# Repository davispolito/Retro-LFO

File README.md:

=======

## The Problem
With only 1-2 wave analog waveforms, LFOs on older synthesizers, specifically the moog prodigy, are severely limited in their capabilities. Since LFOs are control functions and do not directly enter into the audio output, there is no benefit of the circuitry that initially creates these functions. These synthesizers would be better served by a more robust LFO design.
`

## The Solution
Utilizing an Attiny45 I have developed an LFO that can be retrofitted into synthesizers to increase LFO functions. These would include square (bipolar and unipolar), saw, reverse saw, triangle, sine and sample, and hold waveforms. This solution is cost effective using an 8 bit microcontroller that costs under a dollar, and minimal analog components.
 
## The algorithms 
Algorithms for the LFO shapes are simple and concise. By varying a PWM utility on the Attiny, we output a varying pulse square wave that once filtered creates smooth control functions.

### Saw 
```
uint8_t sawtooth(uint8_t* step){
	(*step)++;
	return *step;
}
```

### Reverse Saw
```
uint8_t reversesaw(uint8_t* step){
	(*step)--;

	return *step;
}
```

### Triangle 
```
uint8_t triangle(uint8_t* step){
	static int ud = 0;
	if (ud){
		*step -= 2;
		if(!*step){
			ud = 0;
		}
		} else {
		*step += 2;
		if (*step == 254){
			ud = 1;
		}
	}
	return *step;
}
```

### Unipolar Square 
```
uint8_t square_p(uint8_t* count){
	static int freq = 126;
	(*count)++;
	static uint8_t val = 0x7F;
	if(*count < freq){
		val = 0x7F;
		} else {
		val = 0xFE;
	}
	*count %= 2*freq;

	return val;
}

uint8_t square_n(uint8_t* count){
	static int freq = 126;
	(*count)++;
	static uint8_t val = 0x01;
	if(*count < freq){
		val = 0x01;
		} else {
		val = 0x7F;
	}
	*count %= 2*freq;
	
	return val;
}
```
### Bipolar Square
```
uint8_t square_f(uint8_t* count){

	static int freq = 126;
	(*count)++;
	static uint8_t val = 0x01;
	if(*count < freq){
		val = 0x01;
		} else {
		val = 0xFE;
	}
	*count %= 2*freq;

	return val;
}
```

### Sample and Hold
```
uint8_t sampleAndHold(uint8_t* count){
	static uint8_t b = 0;
	static uint8_t i = 0;
	if(i == 0){
		int a = rand();
		b = 0xFF & a;
	}
	//(*count)++;
	
	return b;
}
``` 
Note: After some time it was determined that the random function was more reliably random than an LFSR. I hope to modify this code to include a modified call to my machine code routine for white noise generation so that I do not need library calls and can keep the program as lightweight as possible. 

### Sine

```
uint8_t sinewave_(uint8_t* i){
	uint8_t val = pgm_read_byte(&sinewave[(*i)++]) / mod_scale + 128 - (256/(mod_scale * 2));
	(*i) %= 256;
	return val;
}
```

## Varying the Frequency
In order to vary the Frequency, I implemented a delay function as well as a mapping function to take my inputs from the ADCs and map them to a piecewise logarithmic modeling function to bring the frequency from 0.3 Hz to 30Hz

 ```
 uint16_t map_m(uint16_t input_end, uint16_t        input_start, uint16_t output_end,               uint16_t output_start,  uint16_t input){
	uint16_t slope = (output_end - output_start) / (input_end - input_start);
	uint16_t output = output_start + slope * (input - input_start);
	return output;
}

int16_t VoltageToDelay (uint16_t volt){
	if(volt < 500){
		return map_m(500, 50, 800, 60, volt);
	} else {
		return map_m(1024, 500, 9200, 700, volt);
	}
	
	return 60 + (volt * 4);			//9000 top value (.3 Hz)  60 - 30 Hz
}

 ```

### Feature Freak
In developing the LFO, we aimed to be as thorough as possible. We utilized all 8 pins on the Attiny45. 

#### 3 Control Pots
By adding a third pot, we tried to implement new effects. One, an amplitude varying waveform based off timing determined by the third pot. We soon learned that reading 3 pots this quickly causes system failure. Delays and skips would occur, ruining our waveform. One possible solution for this would be implementing a rigorous RTOS, though I have yet to attempt implementation.  

Instead, we decided to create a button that would allow modes to be switched and the time varying amplitude to become one of the two control functions, replacing the waveform chooser. It is important that musicians have access to the effects they are using and we hope that this tradeoff will still benefit them.

#### Varying Amplitude with Phase Modulation and Interpolation/Dithering
    The low 12-bit resolution of our PWM forced us to resort to clever bit calculations in an attempt to smooth low amplitude wave forms. As we reduce amplitude, we reduce our bit resolution since we are only afforded smaller values. We are only able to use the least significant byte of our available bits when faced with a signal at half the amplitude. In order to get around this, we attempted a version of interpolation through dithering. When at intermediate phases of a waveform — whenever there are x number of steps between the current sample and the next sample — we switch between the available bits to simulate higher bit resolution.
Unfortunately this did not give us much greater resolution. 

Additionally, in order to create the amplitude variation, we implemented a phasing system. By combining a waveform out of phase with the output waveform, amplitude can be reduced or increased. In order to vary the amplitude, I simply varied the phase of a following waveform until the time step finished. 

```
uint8_t dither_up(uint8_t old_val, uint8_t new_val, uint8_t og_delay, uint8_t curr_delay){
	uint8_t difference = new_val - old_val;
	uint8_t num_cycles = og_delay / CYCLE_US;
	uint8_t curr_cycle = curr_delay / CYCLE_US;
	switch (difference){
		case 1 : {
			if(curr_cycle % 2) {
				return new_val;
				} else {
				return old_val;
			}
			break;
		}
		case 2: {
			uint16_t scaled = (100*curr_cycle) / num_cycles;
			if(scaled <= 33){
				return old_val;
			} else if (scaled <= 66){
				return old_val + 1;
			} else {
				return old_val + 2;
			}
			break;
		}
		case 3: {
			uint16_t scaled = (100*curr_cycle) / num_cycles;
			if(scaled <= 25){
				return old_val;
			} else if (scaled <= 50){
				return old_val + 1;
			} else if (scaled <= 75){
				return old_val + 2;
			} else {
				return old_val + 3;
			}
			break;
		}
	}
}
```
```
uint8_t dither_down(uint8_t old_val, uint8_t new_val, uint8_t og_delay, uint8_t curr_delay){
	uint8_t difference = old_val - new_val;
	uint8_t num_cycles = og_delay / CYCLE_US;
	uint8_t curr_cycle = curr_delay / CYCLE_US;
	switch (difference){
		case 1 : {
			if(curr_cycle % 2) {
				return new_val;
				} else {
				return old_val;
			}
			break;
		}
		default: {
			uint16_t scaled = (100*curr_cycle) / num_cycles;
			if(scaled <= 33){
				return old_val;
				} else if (scaled <= 66){
				return old_val - 1;
				} else {
				return old_val - 2;
			}
			break;
		}
	}
}
```
```
uint8_t dither(int16_t delay, uint8_t old_val){
	uint8_t next_val = wave_ptr(&i);// / mod_scale  + 128 - (256/(mod_scale * 2)); 
	uint8_t h = i + 100;
	uint8_t phaseOffset = wave_ptr(&h);
	//successive approx
	if(half < 16){
		if(next_val >= 128){
			next_val += (256/(mod_scale*half));
		}
		else {
			next_val -= (256/(mod_scale*half));
		}
	}
	int8_t difference;
	uint8_t og_delay = delay;
	while (delay > CYCLE_US * 3){
		if((difference = old_val - next_val) <= 3 && difference > 0){
			OCR0A = dither_down(old_val, next_val, og_delay, delay);
			} else if (difference >= -3 && difference < 0){
			OCR0A = dither_up(old_val, next_val, og_delay, delay);
		}
		_delay_us(CYCLE_US);
		delay = delay - CYCLE_US;
		
	}
	while(delay){
		_delay_us(1);
		delay--;
	}
	uint8_t phased = next_val + phaseOffset;
	if(phased < next_val){
		phased = 256 - phased; 
	}
	return next_val + phased;
}
```

# Future Plans
The plan for the Retro-LFO is to develop a PCB and begin offering it as an enhancement during synthesizer repairs at Retrolinear, as well as market it to eurorack enthusiasts on the web.

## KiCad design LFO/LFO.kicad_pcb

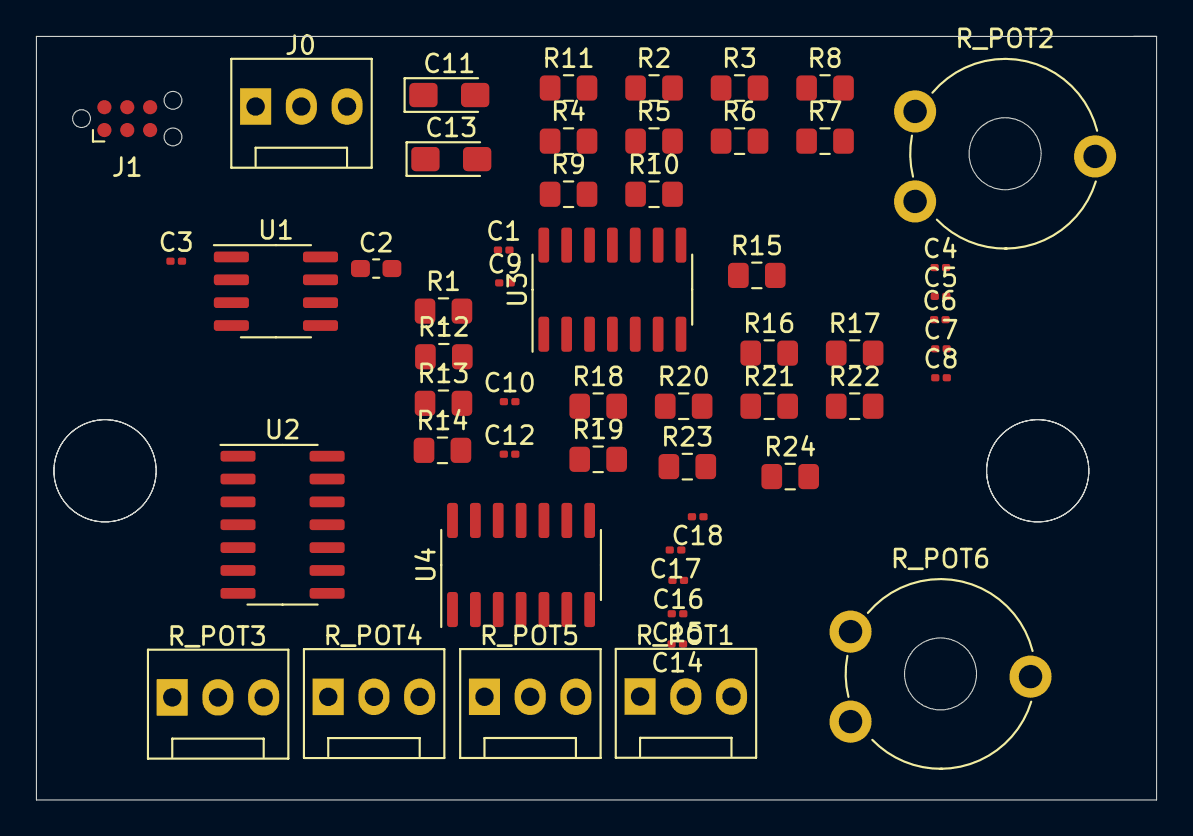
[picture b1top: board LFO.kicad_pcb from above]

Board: 2 copper layers, 62.2 x 42.4 mm, 54 parts (0 on the bottom side), 42 nets, no tracks yet.

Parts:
C1, C4, C9, C10, C12, C14: .1uF; C_0201_0603Metric
C2: .33uF; C_0603_1608Metric_Pad1.05x0.95mm_HandSolder
C3: .01uF; C_0201_0603Metric
C5, C7, C15, C17: 5.6nF; C_0201_0603Metric
C6, C8, C16, C18: 6.8nF; C_0201_0603Metric
C11, C13: 10uF; CP_EIA-3216-10_Kemet-I_Pad1.58x1.35mm_HandSolder
J0: Conn_01x03_Female; FanPinHeader_1x03_P2.54mm_Vertical
J1: AVR-ISP-6; Tag-Connect_TC2030-IDC-NL_2x03_P1.27mm_Vertical
R1, R2, R12, R13, R14, R15: 1k; R_0805_2012Metric_Pad1.15x1.40mm_HandSolder
R3, R4, R5, R6, R16, R17, R18, R19: 20k; R_0805_2012Metric_Pad1.15x1.40mm_HandSolder
R7, R20: 183k; R_0805_2012Metric_Pad1.15x1.40mm_HandSolder
R8, R21: 25k; R_0805_2012Metric_Pad1.15x1.40mm_HandSolder
R9, R11, R22, R24: 220k; R_0805_2012Metric_Pad1.15x1.40mm_HandSolder
R10, R23: 85k; R_0805_2012Metric_Pad1.15x1.40mm_HandSolder
R_POT1, R_POT3, R_POT4, R_POT5: 10k; FanPinHeader_1x03_P2.54mm_Vertical
R_POT2, R_POT6: 10k; Potentiometer_Piher_PT-10-V10_Vertical_Hole
U1: L78L05_SO8; SOIC-8_3.9x4.9mm_P1.27mm
U2: ATtiny44A-PU; SOIC-14_3.9x8.7mm_P1.27mm
U3, U4: TL074; SOIC-14_3.9x8.7mm_P1.27mm

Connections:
5VCC: C3.2, J1.2, R_POT1.1, R_POT3.1, R_POT4.1, R_POT5.1, U1.1, U2.1
/Sheet5E6A635E/output: C1.1, R1.2, U2.13
/Sheet5E71F86A/input: R2.2, U2.5
/Sheet5E71F86A/output: R11.2, U3.14
/sheet5E721A7E/output: C9.1, R12.2, U2.12
/sheet5E721CAD/output: C10.1, R13.2, U2.11
/sheet5E721EDC/output: C12.1, R14.2, U2.10
/sheet5E7293AD/input: R15.2, U2.6
/sheet5E7293AD/output: R24.2, U4.14
AGND: C1.2, C2.2, C3.1, C4.2, C6.2, C8.2, C9.2, C10.2, C11.1, C12.2, C13.2, C14.2, C16.2, C18.2, J0.2, J1.6, R8.2, R21.2, R_POT1.3, R_POT3.3, R_POT4.3, R_POT5.3, U1.2, U1.3, U1.6, U1.7, U2.14, U3.12, U4.12
NEG: C11.2, J0.1, U3.11, U4.11
unnamed: C4.1, R2.1, R3.1
unnamed: C5.1, R5.1, U3.1, U3.2
unnamed: C5.2, R3.2, R4.1
unnamed: C6.1, R4.2, U3.3
unnamed: C7.1, R7.2, U3.6, U3.7
unnamed: C7.2, R5.2, R6.1
unnamed: C8.1, R6.2, U3.5
unnamed: C14.1, R15.1, R16.1
unnamed: C15.1, R18.1, U4.1, U4.2
unnamed: C15.2, R16.2, R17.1
unnamed: C16.1, R17.2, U4.3
unnamed: C17.1, R20.2, U4.6, U4.7
unnamed: C17.2, R18.2, R19.1
unnamed: C18.1, R19.2, U4.5
unnamed: J1.1, U2.8
unnamed: J1.3, U2.9
unnamed: J1.4, U2.7
unnamed: J1.5, U2.4
unnamed: R1.1, R_POT1.2
unnamed: R8.1, R_POT2.1
unnamed: R9.2, R_POT2.2
unnamed: R10.2, R_POT2.3
unnamed: R7.1, R9.1, R11.1, U3.13
unnamed: R12.1, R_POT3.2
unnamed: R13.1, R_POT4.2
unnamed: R14.1, R_POT5.2
unnamed: R20.1, R22.1, R24.1, U4.13
unnamed: R21.1, R_POT6.1
unnamed: R22.2, R_POT6.2
unnamed: R23.2, R_POT6.3
POS: C2.1, C13.1, J0.3, R10.1, R23.1, U1.8, U3.4, U4.4

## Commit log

2019-11-27 README
2019-11-27 Added Circuit Photograph
2020-01-08 Added Schematic
2020-01-08 Added png version of schematic
2020-01-14 Adding Schematic File
2020-02-07 adding duallfo
2020-03-06 Dual LFO and single LFO in working order
